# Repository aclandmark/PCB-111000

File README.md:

# PCB-111000

*/*/*/*/*/*/*/*/*/*/*/*/*/*/*/*/*/*/*/*/*/*/*/*/*/*/*/*/*/*/*/*/*/*/*/*/*/*/*/*/*/*/*/*/*/

This project is now obsolete.     The new version is PCB-111000_V2

The winAVR compiler has been replaced by Arduino and Studio 7

MOSFETS used to drive the display have been dispensed with

The pcb is set up usng a UNO and two sketches both of which are based on the sketch "UNO_as_an_AVR_programer"

Sample user programs have been updated in the light of the change from winAVR to Arduino.

The Nano_projects directory contains projects developed for PCB-111000_V2

*/*/*/*/*/*/*/*/*/*/*/*/*/*/*/*/*/*/*/*/*/*/*/*/*/*/*/*/*/*/*/*/*/*/*/*/*/*/*/*/*/*/*/*/*/*/*/*/

56 Projects for the novice C programmer -   Excludes programmer firm ware

Purpose: To introduce newcomers to C-programming for Atmega micro-controllers using the WinAVR compiler.  Programmers, target devices and a display are all provided on the pcb.  Sample user programs are provided to illustrate various applications such as transferring data to and from a PC, reading switches and driving a display.  Finished projects such as a stop watch, reaction time tester or calculator can be operated independently of a PC provided that a 5V USB supply is available.

PCB 111000 Hardware:

    1. An Atmega 328 that drives an 8 digit 7 segment display and downloads user code to an Atmega 168. 
    2. An Atmega 168 for which the user writes simple C-programs.  
    3. Three switches that can be used to provide inputs for the Atmega 168.
    4. An FTDI 230X USB to UART bridge that enables the PCB to be connected to a PC.
    5. A programming interface:  This is normally used to program the Atmega 168 but can also be used 
       to update the Atmega 328 code.
    6. An I2C interface via which user code controls the display.

PCB 111000 Software:

    1. A basic Atmega programmer that resides in the boot partition of the Atmega 328.
    2. An application that drives the display, hosts an I2C interface and includes other functions 
       including a clock/stop watch and arithmetic (known as the mini-OS).
    3. An Atmega 328 programmer that can be downloaded onto the Atmega 168.
    4. Subroutine library to support user code.

Test_file_change

Link to relevent AVRfreaks project

https://github.com/MicrochipTech/avrfreaks-projects/tree/main/projects/pcb-111000-winavr-taster-pcb

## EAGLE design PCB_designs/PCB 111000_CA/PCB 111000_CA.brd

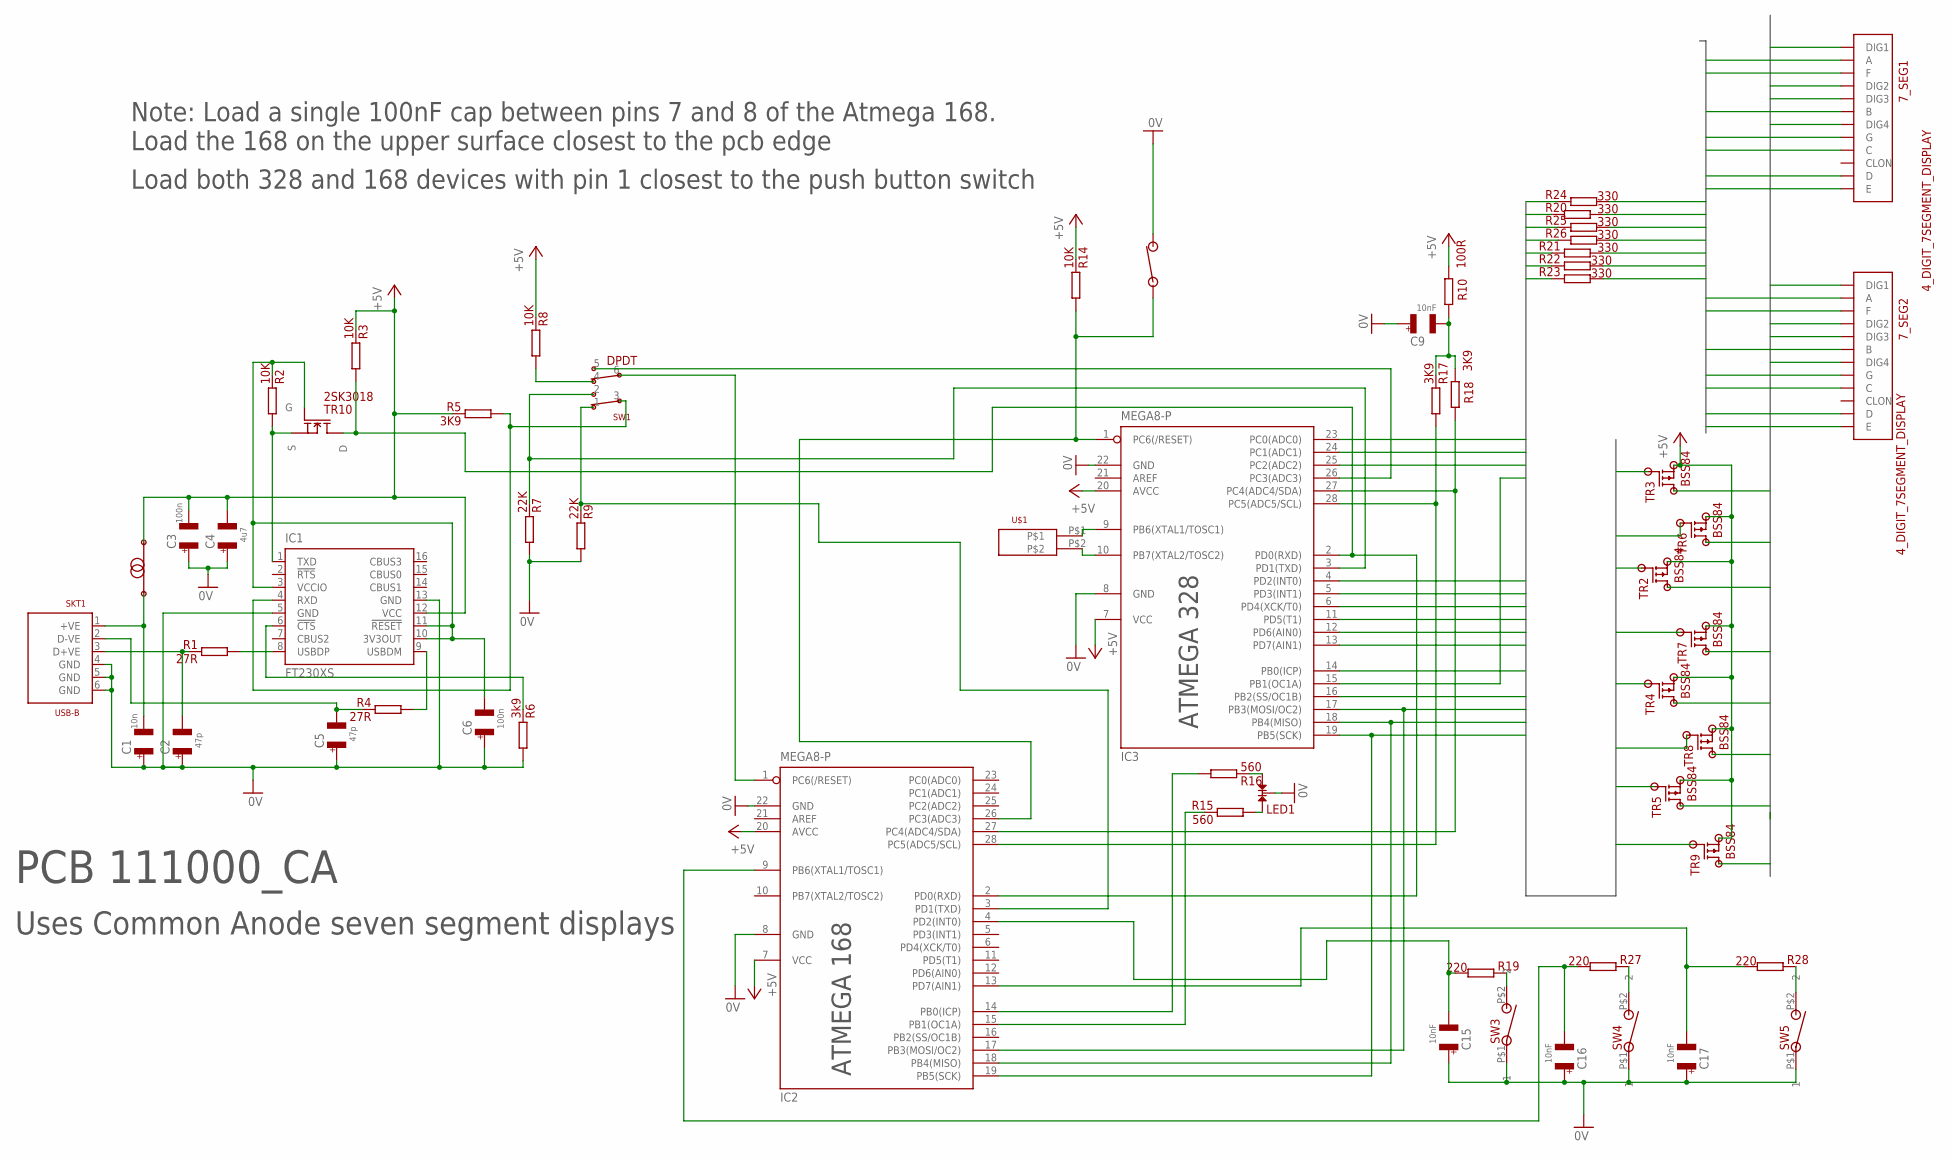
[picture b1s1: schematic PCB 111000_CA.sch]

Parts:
7_SEG1, 7_SEG2: 4_DIGIT_7SEGMENT_DISPLAY
C1: 10n; 1206
C2, C5: 47p; 1206
C3, C6: 100n; 1206
C4: 4u7; 1206
C9, C15, C16, C17: 10nF; 1206
IC1: FT230XS; SSOP16
IC2, IC3: MEGA8-P; DIL28-3
L1: CHOKE; 1206
LED1: LED; CA_DUAL_LED
R1, R4: 27R; 1206
R2, R3, R8, R14: 10K; 1206
R5, R17, R18: 3K9; 1206
R6: 3k9; 1206
R7, R9: 22K; 1206
R10: 100R; 1206
R15, R16: 560; 1206
R19, R27, R28: 220; 1206
R20, R21, R22, R23, R24, R25, R26: 330; 1206
SKT1: USB-B
SW1: DPDT; DPDT_SWITCH
SW2: NO_SW; SM_NO_PUSH_BUTTON
SW3, SW4, SW5: NO_PB_1; RE51-0711
TR2, TR3, TR4, TR5, TR6, TR7, TR8, TR9: BSS84; SOT23
TR10: 2SK3018
U$1: XTAL; XTAL_VIAS

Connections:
0V: C1.P$1 (1), C2.P$1 (1), C3.P$1 (1), C4.P$1 (1), C5.P$1 (1), C6.P$1 (1), C9.P$1 (1), C15.P$1 (1), C16.P$1 (1), C17.P$1 (1), IC1.5 (GND), IC1.13 (GND), IC2.8 (GND), IC2.22 (GND), IC3.8 (GND), IC3.22 (GND), LED1.2, R6.P$1, R7.P$1, R9.P$1, SKT1.4 (GND), SKT1.5 (GND), SKT1.6 (GND), SW2.P$2 (2), SW3.P$1 (1), SW4.P$1 (1), SW5.P$1 (1)
+5V: C3.P$2 (2), C4.P$2 (2), IC1.12 (VCC), IC2.7 (VCC), IC2.20 (AVCC), IC3.7 (VCC), IC3.20 (AVCC), L1.P$2 (2), R3.P$2, R5.P$2, R8.P$2, R10.P$2, R14.P$2, TR2.2 (S), TR3.2 (S), TR4.2 (S), TR5.2 (S), TR6.2 (S), TR7.2 (S), TR8.2 (S), TR9.2 (S)
DIGIT0: 7_SEG1.P$12 (DIG1), TR4.3 (D)
DIGIT1: 7_SEG1.P$9 (DIG2), TR8.3 (D)
DIGIT2: 7_SEG1.P$8 (DIG3), TR5.3 (D)
DIGIT3: 7_SEG1.P$6 (DIG4), TR9.3 (D)
DIGIT4: 7_SEG2.P$12 (DIG1), TR3.3 (D)
DIGIT5: 7_SEG2.P$9 (DIG2), TR6.3 (D)
DIGIT6: 7_SEG2.P$8 (DIG3), TR2.3 (D)
DIGIT7: 7_SEG2.P$6 (DIG4), TR7.3 (D)
DISPLAY_DRIVER0: IC3.15 (PB1(OC1A)), R24.P$2
DISPLAY_DRIVER1: IC3.4 (PD2(INT0)), R20.P$2
DISPLAY_DRIVER2: IC3.5 (PD3(INT1)), R25.P$2
DISPLAY_DRIVER3: IC3.6 (PD4(XCK/T0)), R26.P$2
DISPLAY_DRIVER4: IC3.11 (PD5(T1)), R21.P$2
DISPLAY_DRIVER5: IC3.12 (PD6(AIN0)), R22.P$2
DISPLAY_DRIVER6: IC3.13 (PD7(AIN1)), R23.P$2
DISPLAY_DRIVER8: IC3.14 (PB0(ICP)), TR3.1 (G)
DISPLAY_DRIVER9: IC3.16 (PB2(SS/OC1B)), TR6.1 (G)
DISPLAY_DRIVER10: IC2.17 (PB3(MOSI/OC2)), IC3.17 (PB3(MOSI/OC2)), TR2.1 (G)
DISPLAY_DRIVER11: IC2.18 (PB4(MISO)), IC3.18 (PB4(MISO)), TR7.1 (G)
DISPLAY_DRIVER12: IC2.19 (PB5(SCK)), IC3.19 (PB5(SCK)), TR4.1 (G)
DISPLAY_DRIVER13: IC3.23 (PC0(ADC0)), TR8.1 (G)
DISPLAY_DRIVER14: IC3.24 (PC1(ADC1)), TR5.1 (G)
DISPLAY_DRIVER15: IC3.25 (PC2(ADC2)), TR9.1 (G)
unnamed: IC2.14 (PB0(ICP)), R16.P$1
unnamed: IC2.15 (PB1(OC1A)), R15.P$2
unnamed: LED1.1, R15.P$1
unnamed: LED1.3, R16.P$2
unnamed: IC3.26 (PC3(ADC3)), SW1.5
unnamed: IC3.3 (PD1(TXD)), R7.P$2, SW1.2
unnamed: R27.P$2, SW4.P$2 (2)
unnamed: R19.P$2, SW3.P$2 (2)
unnamed: C6.P$2 (2), IC1.3 (VCCIO), IC1.10 (3V3OUT), IC1.11 (!RESET), R2.P$2, TR10.2 (G)
unnamed: IC3.9 (PB6(XTAL1/TOSC1)), U$1.P$1
unnamed: C17.P$2 (2), IC2.13 (PD7(AIN1)), R28.P$1
unnamed: IC3.10 (PB7(XTAL2/TOSC2)), U$1.P$2
unnamed: R8.P$1, SW1.4
unnamed: IC2.3 (PD1(TXD)), R9.P$2, SW1.1
unnamed: IC1.1 (TXD), R2.P$1, TR10.1 (S)
unnamed: R28.P$2, SW5.P$2 (2)
unnamed: C15.P$2 (2), IC2.4 (PD2(INT0)), R19.P$1
unnamed: IC1.9 (USBDM), R4.P$1
unnamed: C16.P$2 (2), IC2.9 (PB6(XTAL1/TOSC1)), R27.P$1
unnamed: C9.P$2 (2), R10.P$1, R17.P$2, R18.P$2
unnamed: IC1.8 (USBDP), R1.P$1
unnamed: IC2.1 (PC6(/RESET)), SW1.6
unnamed: C5.P$2 (2), R4.P$2, SKT1.2 (D-VE)
unnamed: C2.P$2 (2), R1.P$2, SKT1.3 (D+VE)
unnamed: C1.P$2 (2), L1.P$1 (1), SKT1.1 (+VE)
unnamed: IC2.26 (PC3(ADC3)), IC3.1 (PC6(/RESET)), R14.P$1, SW2.P$1 (1)
unnamed: IC1.6 (!CTS), R6.P$2
unnamed: IC1.4 (RXD), R5.P$1, SW1.3
unnamed: IC2.28 (PC5(ADC5/SCL)), IC3.28 (PC5(ADC5/SCL)), R17.P$1
unnamed: IC2.27 (PC4(ADC4/SDA)), IC3.27 (PC4(ADC4/SDA)), R18.P$1
unnamed: IC2.2 (PD0(RXD)), IC3.2 (PD0(RXD)), R3.P$1, TR10.3 (D)
SEVEN_SEG0: 7_SEG1.P$11 (A), 7_SEG2.P$11 (A), R24.P$1
SEVEN_SEG1: 7_SEG1.P$7 (B), 7_SEG2.P$7 (B), R20.P$1
SEVEN_SEG2: 7_SEG1.P$4 (C), 7_SEG2.P$4 (C), R25.P$1
SEVEN_SEG3: 7_SEG1.P$2 (D), 7_SEG2.P$2 (D), R26.P$1
SEVEN_SEG4: 7_SEG1.P$1 (E), 7_SEG2.P$1 (E), R21.P$1
SEVEN_SEG5: 7_SEG1.P$10 (F), 7_SEG2.P$10 (F), R22.P$1
SEVEN_SEG6: 7_SEG1.P$5 (G), 7_SEG2.P$5 (G), R23.P$1

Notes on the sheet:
Note: Load a single 100nF cap between pins 7 and 8 of the Atmega 168. Load the 168 on the upper surface closest to the pcb edge
Load both 328 and 168 devices with pin 1 closest to the push button switch
ATMEGA 168
ATMEGA 328
PCB 111000_CA
Uses Common Anode seven segment displays

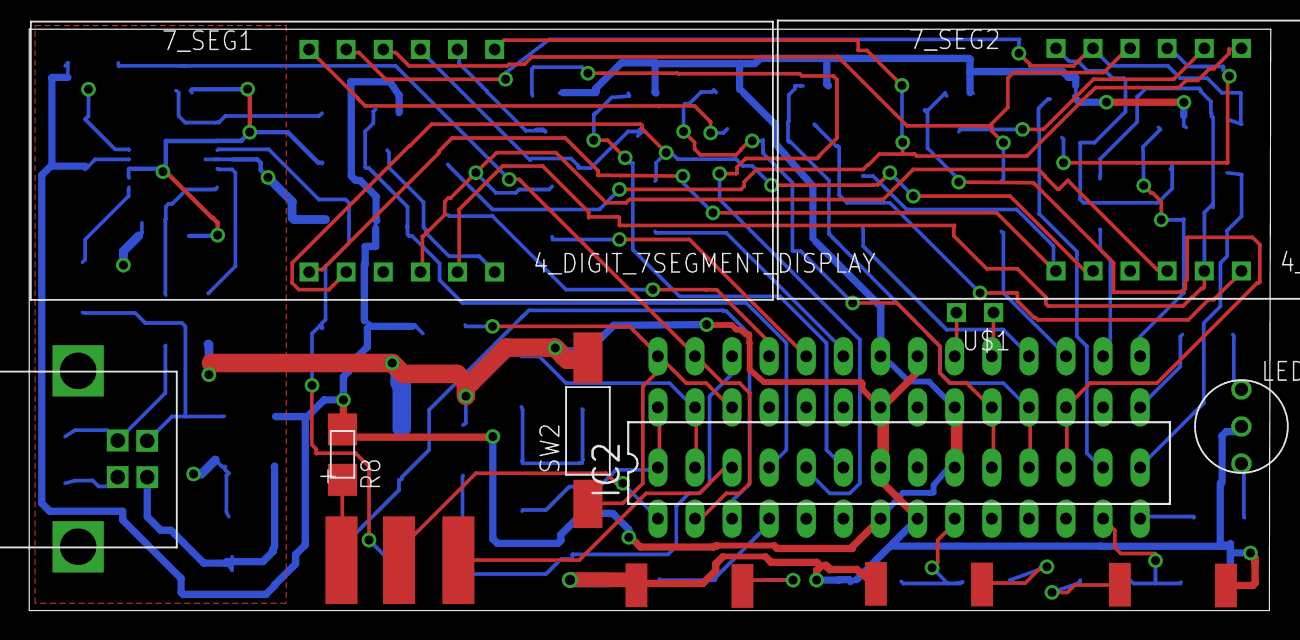
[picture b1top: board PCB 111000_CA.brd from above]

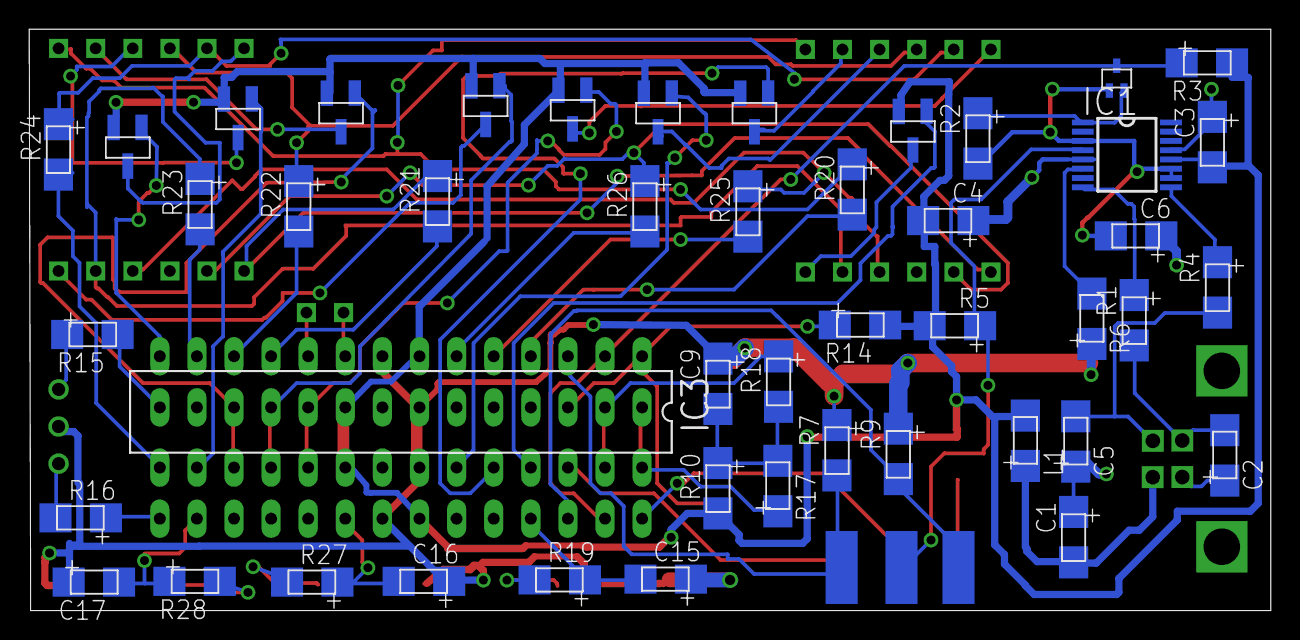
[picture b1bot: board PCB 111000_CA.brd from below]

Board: 2 copper layers, 85.0 x 39.8 mm, 58 parts (47 on the bottom side), 63 nets.

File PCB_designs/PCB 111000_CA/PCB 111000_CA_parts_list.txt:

Partlist

Two versions of PCB 111000 are available
PCB 111000_CC uses Common Cathode displays 
PCB 111000_CA Common Anode displays

PCB 2 layer board 85mm by 40mm

7_SEG1&2  CA56-12SURKWA	RS872-1907 or RS146-1581  or 872_1907P	Common Anode Red display		

IC1      FT230XS   	RS 757-0010 
IC2      ATMEGA 168 	RE 73-4276                              
IC3      ATMEGA 328    	RE 73-4281   
L1       CHOKE		RS 724-1582                    

BSS84		RS 436-8091P		TR2-9			8 OFF
2SK3018		RS 694-2812		TR10     		1 OFF

27R 		RS 679-1979		R1, R4			2 OFF
100R 		RS 223-2120		R10			1 OFF
220R 		RS 153-987		R19, R27, R28		3 OFF	(switch decoupling)	
330R		RS 721-9784
220R		RS 123-4356		R20-26			7 OFF (Segment drivers) 
560R 		RS 679-2225		R15,16			2 OFF	(dual LED drivers)
3K9  		RS 223-2344		R5-6, R17-18		4 OFF	
10K  		RS 223-2394		R2-3, R8, R14		4 OFF
22K 		RS 679-1917		R7, R9			2 OFF

18pF		RS 648-0935					2 off for crystal
47p		RS 391-028		C2, C5			2 OFF
10n		RS 264-4141		C1, C9, C15-17		5 OFF
100n		RS 264-4179		C3, C6			2 OFF + Extra decoupling
4.7uF		RS 691-1224		C4			1 OFF
1uF		RS 648-0733		Additional decoupling to IC pins
Xtal		RS 547-6985 or 478-9268	

SW1		RE 76-0100	DPDT							
SW2		RE 51-0709	NO push button (SM)		
SW3-5		RE51-0711	NO push button (with pins)	 

SKT1		RS 515-1967	USB socket			

LED1		RS228-5764 	CC_DUAL_LED (There is an error in the library. No worry!!)


Note RS is Radio Spares and RE is Rapid Electronics

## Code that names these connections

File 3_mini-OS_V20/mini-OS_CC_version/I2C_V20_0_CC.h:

#include <avr/io.h>
#include <stdlib.h>
#include <avr/interrupt.h>
#include <avr/wdt.h>
#include <avr/eeprom.h>

volatile char payload_size;							//zero to hide clock, 1 to update 10mS 2 to update 100ms and 8 to update seconds
volatile int disp_ptr;
volatile char Char_received, exit_loop = 0, display_mask;		//ISR UART
volatile char mode=1, timer_mode, inc_secs, inc_mins;					//ISR T0
volatile char display_buf[8], clock_buf[8], stop_watch_buf[8],strobe[8];
volatile int buf_ptr, mode_C_ptr;
volatile char T1_ovf_flag=0, timer_2_counter;
volatile signed char output_2;
volatile int Ten_mS_tick = 41;
unsigned long number[6];
signed char exponent[3];

void I2C_master_transmit(char);
char I2C_master_receive(char);
void basic_clock (void);
void multi_mode_clock(void);
void stop_watch(void);
void Message_from_the_OS(void);
void cal_plot_328(void);
void manual_cal_PCB_A_device(void);
void spot_check_328_cal(void);
void start_T2_for_ATMEGA_168_cal(char);


volatile char entry_point;
char Sc_Num_string[16];
int Sc_Num_string_length, Sc_Num_string_pointer, display_char_skip_counter;

volatile int EA_counter, EA_buff_ptr;
int buffer[41];	//Used to store "long" results, however for this application results are always less than 32000
volatile char T1_OVF;
volatile long error_SUM;
char OSCCAL_test;
volatile char MUX_cntl, T0_interupt_cnt;



char I2C_data[10];

char  display_backup[9];
signed char exponent_BKP[2];
int RN;
char keypres_counter_old;
char overflow;

char Op;
unsigned long RHSofDP;
signed char expnt_result;
char result[4];
int accumlator;
int interim_result;

char OSCCAL_WV;
char OSCCAL_DV, OSCCAL_UC;
long cal_error;	

char clock_flag=0, stop_watch_flag, PIC_cmd, Ten_mS_tick_counter = 0, stop_watch_mode;

#define setup_watchdog;\
wdr();\
MCUSR &= ~(1<<WDRF);\
WDTCSR |= (1 <<WDCE) | (1<< WDE);\
WDTCSR = 0;

#define wdr()  __asm__ __volatile__("wdr")


#define initialise_IO;\
MCUCR &= (~(1 << PUD));\
DDRB = 0;\
DDRC = 0;\
DDRD = 0;\
PORTB = 0xFF;\
PORTC = 0xFF;\
PORTD = 0xFF;\
PORTC &= (~(1 << PC3));	



#define initialise_Arithmetic_variables; \
exponent_BKP[0]=0; exponent_BKP[1]=0;\
expnt=0;\
Op = 0;\
accumlator=0;\
RN=0;keypres_counter_old=0; overflow=0;\
RHSofDP = 0;expnt_result = 0;




#define two_fifty_mS_delay; timer_T1_sub_with_interrupt(T1_delay_250ms);while (T1_ovf_flag == 0);T1_ovf_flag = 0;
#define T1_delay_250ms 5,0xF861
#define two_fifty_mS_delay_with_interrupts; TIMSK1 |= (1 << TOIE1);two_fifty_mS_delay; TIMSK1 &= (~(1 << TOIE1));

#define one_sec_delay; timer_T1_sub_with_interrupt(T1_delay_1sec);while (T1_ovf_flag == 0);T1_ovf_flag = 0;
#define T1_delay_1sec 5,0xE17B
#define one_sec_delay_with_interrupts; TIMSK1 |= (1 << TOIE1);one_sec_delay; TIMSK1 &= (~(1 << TOIE1));

#define	digit_3		PORTB |= (1 << PB0);
#define	digit_2		PORTB |= (1 << PB2);
#define	digit_1		PORTB |= (1 << PB3);
#define	digit_0		PORTB |= (1 << PB4);

#define	digit_7		PORTB |= (1 << PB5);
#define	digit_6		PORTC |= (1 << PC0);
#define	digit_5		PORTC |= (1 << PC1);
#define	digit_4		PORTC |= (1 << PC2);

#define	seg_a 	(1 << PB1)
#define	seg_b 	(1 << PD2)
#define	seg_c 	(1 << PD3)
#define	seg_d 	(1 << PD4)
#define	seg_e 	(1 << PD5)
#define	seg_f 	(1 << PD6)
#define	seg_g 	(1 << PD7)

#define set_digit_drivers;\
DDRB |= (1 << DDB0) | (1 << DDB1) | (1 << DDB2) | (1 << DDB3) | (1 << DDB4) | (1 << DDB5);\
DDRC |= (1 << DDC0) | (1 << DDC1) | (1 << DDC2);\
DDRD |= (1 << DDD2) | (1 << DDD3) | (1 << DDD4) | (1 << DDD5) | (1 << DDD6) | (1 << DDD7);

#define clear_digits; PORTB &= (~((1 << PB0) | (1 << PB2) | (1 << PB3) | (1 << PB4) | (1 << PB5)));\
PORTC &= (~((1 << PC0) | (1 << PC1) | (1 << PC2)));

#define clear_display; PORTB &= (~(seg_a ));\
PORTD &= (~(seg_b | seg_c | seg_d | seg_e | seg_f | seg_g));

#define clear_display_buffer; for(int m = 0; m<=7; m++)display_buf[m] = 0;

#define one_U 	PORTD |= (seg_b);
#define ONE_U 	PORTD |= (seg_f);
#define one_L 	PORTD |= (seg_c);
#define ONE_L 	PORTD |= (seg_e);
#define ONE		PORTD |= (seg_e | seg_f);
#define one 	PORTD |= (seg_b | seg_c);
#define two 	PORTB |= (seg_a); PORTD |= (seg_b | seg_d | seg_e | seg_g);
#define three 	PORTB |= (seg_a); PORTD |= (seg_b | seg_c | seg_d | seg_g);
#define four 	PORTD |= (seg_b | seg_c | seg_f | seg_g);
#define five 	PORTB |= (seg_a); PORTD |= (seg_c | seg_d | seg_f | seg_g);
#define six 	PORTD |= (seg_c | seg_d | seg_e | seg_f | seg_g);
#define seven 	PORTB |= (seg_a); PORTD |= (seg_b | seg_c );
#define eight 	PORTB |= (seg_a);  PORTD |= (seg_b | seg_c | seg_d | seg_e | seg_f | seg_g);
#define nine	PORTB |= (seg_a); PORTD |= (seg_b | seg_c | seg_f | seg_g);
#define zero	PORTB |= (seg_a); PORTD |= (seg_b | seg_c | seg_d | seg_e | seg_f );
#define decimalP	PORTB |= (seg_a);	PORTD |= (seg_b | seg_e | seg_f | seg_g );


#define T0_delay_33ms 5,0
#define T0_delay_20ms 5,100
#define T0_delay_16ms 5,131
#define T0_delay_12ms 5,162
#define T0_delay_10ms 5,178
#define T0_delay_8ms 5,194
#define T0_delay_6ms 4,70
#define T0_delay_5ms 4,100
#define T0_delay_4ms 4,130
#define T0_delay_3ms 4,162
#define T0_delay_2500us 4,178
#define T0_delay_2ms 3,0
#define T0_delay_1500us 3,69
#define T0_delay_1ms 3,128
#define T0_delay_667us 3,173
#define T0_delay_500us 3,194
#define T0_delay_250us 2,6

#define T1_delay_500ms 5, 0xF0C3
#define T1_delay_10ms 3, 0xF63C

#define refresh_clock_display;   for (int n = 0; n < 8; n++){display_buf[n] = clock_buf[n];}
#define refresh_stop_watch_display;  for (int n = 0; n < 8; n++){display_buf[n] = stop_watch_buf[n];}
#define initiate_stop_watch_display;  for (int n = 0; n < 8; n++){stop_watch_buf[n] = '0';}

#define increment_seconds;	if (clock_buf[0] < '9') clock_buf[0]++; else {clock_buf[0] = '0';\
if (clock_buf[1] < '5') clock_buf[1]++;else {clock_buf[1] = '0';\
if (clock_buf[3] < '9') clock_buf[3]++; else {clock_buf[3] = '0';\
if (clock_buf[4] < '5') clock_buf[4]++;else {clock_buf[4] = '0';}}}}

#define decrement_seconds; if (clock_buf[0] > '0') clock_buf[0]--; else {clock_buf[0] = '9';\
if (clock_buf[1] > '0') clock_buf[1]--; else {clock_buf[1] = '5';\
if (clock_buf[3] > '0') clock_buf[3]--; else {clock_buf[3] = '9';\
if (clock_buf[4] > '0') clock_buf[4]--;else {clock_buf[4] = '5';}}}}


#define increment_minutes; if (clock_buf[3] < '9') clock_buf[3]++; else {clock_buf[3] = '0';\
if (clock_buf[4] < '5') clock_buf[4]++;else {clock_buf[4] = '0';\
switch (clock_buf[7]){\
case '0': case '1': if (clock_buf[6] < '9') clock_buf[6]++; else {clock_buf[6] = '0';clock_buf[7]++;}break;\
case '2': if (clock_buf[6] < '3') clock_buf[6]++; else {clock_buf[6] = '0';clock_buf[7] = '0';}}}}


#define decrement_minutes; if (clock_buf[3] > '0') clock_buf[3]--; else {clock_buf[3] = '9';\
if (clock_buf[4] > '0') clock_buf[4]--;else {clock_buf[4] = '5';\
switch (clock_buf[7]){\
case '1': case '2': if (clock_buf[6] > '0') clock_buf[6]--; else {clock_buf[6] = '9';clock_buf[7]--;}break;\
case '0': if (clock_buf[6] > '0') clock_buf[6]--; else {clock_buf[6] = '3';clock_buf[7] = '2';}}}}


#define Initialise_I2C_master_write;\
	while(1){\
	TWCR = (1 << TWINT) | (1 << TWSTA) | (1 << TWEN);\
	while (!(TWCR & (1 << TWINT)));\
	TWDR = 0x02;\
	TWCR = (1 << TWINT) | (1 << TWEN);\
	while (!(TWCR & (1 << TWINT)));\
	if (TWSR == 0x18)break;	}	
	
#define Initialise_I2C_master_read;\
	while(1){\
	TWCR = (1 << TWINT) | (1 << TWSTA) | (1 << TWEN);\
	while (!(TWCR & (1 << TWINT)));\
	TWDR = 0x03;\
	TWCR = (1 << TWINT) | (1 << TWEN);\
	while (!(TWCR & (1 << TWINT)));\
	if (TWSR == 0x40)break;	}


#define long_to_slave_I2C;\
	while(1){\
	TWCR = (1 << TWINT) | (1 << TWSTA) | (1 << TWEN);\
	while (!(TWCR & (1 << TWINT)));\
	TWDR = 0x02;\
	TWCR = (1 << TWINT) | (1 << TWEN);\
	while (!(TWCR & (1 << TWINT)));\
	if (TWSR == 0x18)break;	}\
	for(int m = 0; m<=3; m++)\
	{TWDR = result[m];\
	TWCR = (1 << TWINT) | (1 << TWEN);\
	while (!(TWCR & (1 << TWINT)));}\
	TWCR = (1 << TWINT) | (1 << TWEN) | (1 << TWSTO);	




		

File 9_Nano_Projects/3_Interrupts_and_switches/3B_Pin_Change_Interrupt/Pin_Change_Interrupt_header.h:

#include <avr/wdt.h>

char watch_dog_reset = 0;

#define T0_delay_10ms 5,178
#define T1_delay_100ms 3, 0x9E62
#define T2_delay_10ms 7,178


#define set_up_PCI_on_sw2           PCICR |= (1 << PCIE0);
#define enable_pci_on_sw2           PCMSK0 |= (1 << PCINT6);


#define switch_1_down  ((PIND & 0x80)^0x80)
#define switch_1_up   (PIND & 0x80)
#define switch_3_down ((PIND & 0x04)^0x04)
#define switch_3_up   (PIND & 0x04)
#define switch_2_down ((PINB & 0x40)^0x40)
#define switch_2_up   (PINB & 0x40)

/*****************************************************************************/
#define setup_HW \
setup_watchdog;\
set_up_I2C;\
ADMUX |= (1 << REFS0);\
set_up_switched_inputs;\
Set_LED_ports;\
Unused_I_O;\
eeprom_write_byte((uint8_t*)(0x1FD),OSCCAL);\
while (!(PIND & (1 << PD1)));\
Timer_T0_10mS_delay_x_m(5);\
OSC_CAL;\
setup_PC_comms_Basic(0,16);\
I2C_Tx_LED_dimmer();



/*****************************************************************************/
#define setup_HW_Extra \
setup_HW;\
\
Timer_T0_10mS_delay_x_m(1);\
I2C_TX_328_check();\
waiting_for_I2C_master;\
if (receive_byte_with_Nack()==1)\
{TWCR = (1 << TWINT);\
String_to_PC_Basic("\r\nPress\r\n\
1 for OS version\r\n\
2 for system data\r\n\
3 Message from the OS (x to escape)\r\n\
4 Default project\r\n\
0 to escape\r\n");\
switch (waitforkeypress_Basic()){\
case '0':break;\
case '1':I2C_Rx_get_version('0');break;\
case '2':I2C_Rx_get_version('1');break;\
case '3':do\
{Read_Hello_world_string();newline_Basic();}\
while (waitforkeypress_Basic() != 'x');\
break;\
case '4':wdt_enable(WDTO_30MS);\
I2C_Tx_display(); break;}}\
else TWCR = (1 << TWINT);



/*****************************************************************************/
#define setup_watchdog \
if (MCUSR & (1 << WDRF))watch_dog_reset = 1;\
wdr();\
MCUSR &= ~(1<<WDRF);\
WDTCSR |= (1 <<WDCE) | (1<< WDE);\
WDTCSR = 0;

#define wdr()  __asm__ __volatile__("wdr")

#define SW_reset {wdt_enable(WDTO_30MS);while(1);}



/*****************************************************************************/
#define set_up_I2C \
TWAR = 0x02;



/*****************************************************************************/
#define set_up_switched_inputs \
MCUCR &= (~(1 << PUD));\
DDRD &= (~((1 << PD2)|(1 << PD7)));\
PORTD |= ((1 << PD2) | (1 << PD7));\
DDRB &= (~(1 << PB6));\
PORTB |= (1 << PB6);



/*****************************************************************************/
#define Unused_I_O \
MCUCR &= (~(1 << PUD));\
DDRB &= (~((1 << PB2)|(1 << PB7)));\
DDRC &= (~((1 << PC0)|(1 << PC1)|(1 << PC2)));\
DDRD &= (~((1 << PD3)|(1 << PD4)|(1 << PD5)|(1 << PD6)));\
PORTB |= ((1 << PB2)|(1 << PB7));\
PORTC |= ((1 << PC0)|(1 << PC1)|(1 << PC2));\
PORTD |= ((1 << PD3)|(1 << PD4)|(1 << PD5)|(1 << PD6));



/*****************************************************************************/
#define Set_LED_ports   DDRB = (1 << DDB0) | (1 << DDB1);
#define LEDs_on       PORTB |= (1 << PB0)|(1 << PB1);
#define LEDs_off      PORTB &= (~((1 << PB0)|(1 << PB1)));
#define LED_1_on      PORTB |= (1 << PB1);
#define LED_1_off     PORTB &= (~( 1<< PB1)); 
#define LED_2_off     PORTB &= (~(1 << PB0));
#define LED_2_on      PORTB |= (1 << PB0);

#define Toggle_LED_1 \
if (PORTB & (1 << PB1)){LED_1_off;}\
else {PORTB |= (1 << PB1);}



/*****************************************************************************/
#define OSC_CAL \
if ((eeprom_read_byte((uint8_t*)0x1FE) > 0x0F)\
&&  (eeprom_read_byte((uint8_t*)0x1FE) < 0xF0) && (eeprom_read_byte((uint8_t*)0x1FE)\
== eeprom_read_byte((uint8_t*)0x1FF))) {OSCCAL = eeprom_read_byte((uint8_t*)0x1FE);}



/*****************************************************************************/
#define diagnostic_mode \




/*****************************************************************************/
#define waiting_for_I2C_master \
TWCR = (1 << TWEA) | (1 << TWEN);\
while (!(TWCR & (1 << TWINT)));\
TWDR;

#define clear_I2C_interrupt \
TWCR = (1 << TWINT);



/*****************************************************************************/
#include "Resources_nano_projects/Subroutines/HW_timers.c"
#include "Resources_nano_projects/PC_comms/Basic_Rx_Tx_Basic.c"
#include "Resources_nano_projects/I2C_Subroutines/I2C_subroutines_1.c"
#include "Resources_nano_projects/I2C_Subroutines/I2C_subroutines_2.c"
#include "Resources_nano_projects/I2C_Subroutines/I2C_slave_Rx_Tx.c"
#include "Resources_nano_projects/I2C_Subroutines/I2C_diagnostic.c"
#include "Resources_nano_projects/Subroutines/Random_and_prime_nos.c"




/******************************************************************************/

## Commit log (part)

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2023-06-24 Create PCB 111000_CC.b##
2023-06-24 Create .~lock.7_EEPROM allocations.odt#
2023-06-24 Create .~lock.PCB111000_investigation.odt#
2023-06-24 Update .~lock.PCB111000_investigation.odt#
2023-06-26 Create I2C_V20_0_CA_part_1
2023-06-26 Create I2C_V20_0_CA_part_2
2023-06-26 Create I2C_V20_0_CC_part_1
2023-06-26 Create I2C_V20_0_CC_part_2
2023-06-26 Create makefile
